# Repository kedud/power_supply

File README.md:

# Power Supply

Symetrical +15/-15V power supply intented to power RM4 mixer.

Some of the part are not present on the schematic:
 - Fuse
 - IEC panel mount adapter
 - DIN panel mount output connector
 - Power switch
 - Case

| Parts 			| 	 Part ref		|
| ----------------- | ----------------- |
| Fuse 				|               	|
| IEC connector 	|               	|
| DIN connector 	|               	|
| Power switch		|					|

The BoM for this schematics can be found [here](https://octopart.com/bom-tool/Scw2LM2J)

A Mouser cart is also available [here](https://www.mouser.com/ProjectManager/ProjectDetail.aspx?AccessID=ff7172ce4d)

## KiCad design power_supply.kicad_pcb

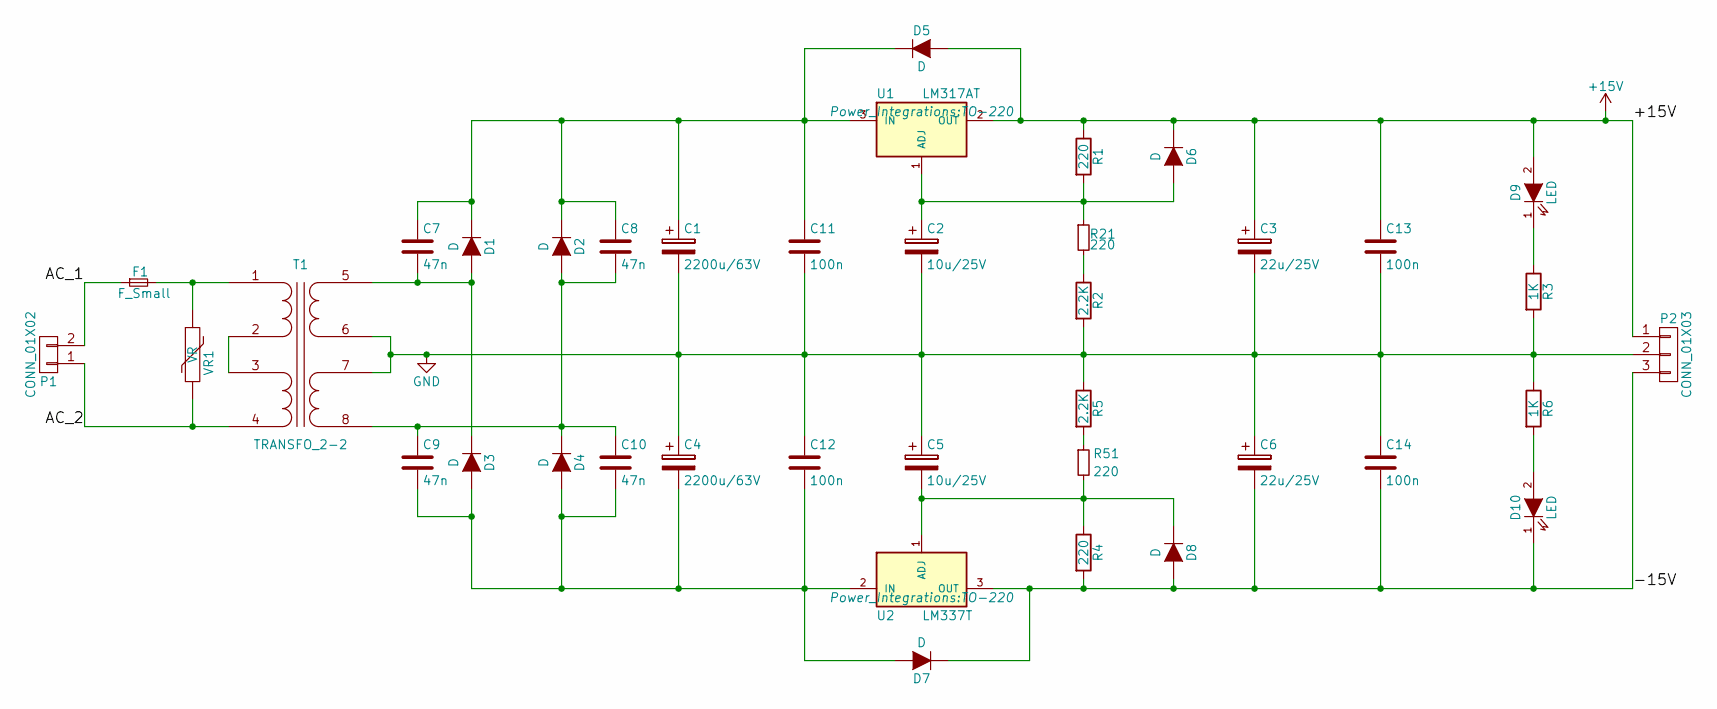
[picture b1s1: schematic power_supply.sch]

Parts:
C1, C4: 2200u/63V; C_Radial_D18_L36_P7.5; Mfg_Part_No UVR1J222MHD
C2, C5: 10u/25V; C_Radial_D5_L11_P2; Mfg_Part_No TVX1E101MAD
C3, C6: 22u/25V; C_Radial_D5_L11_P2; Mfg_Part_No UVR1E220MDD
C7, C8, C9, C10: 47n; C_Rect_L7_W4.5_P5; Mfg_Part_No QYX2A473KTP
C11, C12, C13, C14: 100n; C_Rect_L7_W4.5_P5; Mfg_Part_No QYX2A104KTP
D1, D2, D3, D4: D; Diode_DO-35_SOD27_Horizontal_RM10; Mfg_Part_No BY255P-E3/54 BY255P-E3/54
D5, D6, D7, D8: D; Diode_DO-35_SOD27_Horizontal_RM10; Mfg_Part_No 1N4007
D9, D10: LED; LED-3MM
F1: F_Small; CP4; Mfg_Part_No 0031.1666
P1: CONN_01X02; CONN_2; Mfg_Part_No PX0580/28
P2: CONN_01X03; CONN_3
R1, R4: 220; Resistor_Horizontal_RM7mm; Mfg_Part_No 0
R2, R5: 2.2K; Resistor_Horizontal_RM7mm; Mfg_Part_No CCF072K20JKE36
R3: 1K; Resistor_Horizontal_RM7mm
R6: 1K; Resistor_Horizontal_RM7mm; Mfg_Part_No 0
R21, R51: 220; Resistor_Horizontal_RM7mm
T1: TRANSFO_2-2; TRANSF-4x4; Mfg_Part_No FS36-550-C2 FS36-550-C2 FS36-550-C2
U1: LM317AT; TO-220; Mfg_Part_No LM317KCSE3 LM317KCSE3
U2: LM337T; TO-220; Mfg_Part_No LM337T/NOPB
VR1: VR; Resistor_Horizontal_RM7mm; Mfg_Part_No V250LA40AP

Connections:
+15V: C3.1, C13.1, D5.2 (A), D6.1 (K), D9.2 (A), P2.1, R1.1, U1.2 (OUT)
/-15V: C6.2, C14.2, D7.1 (K), D8.2 (A), D10.1 (K), P2.3, R4.2, U2.3 (OUT)
/AC_1: F1.1, P1.2
/AC_2: P1.1, T1.4 (PD), VR1.2
GND: C1.2, C2.2, C3.2, C4.1, C5.1, C6.1, C11.2, C12.1, C13.2, C14.1, P2.2, R2.2, R3.2, R5.1, R6.1, T1.6 (SB), T1.7 (SC)
unnamed: C1.1, C7.1, C8.1, C11.1, D1.1 (K), D2.1 (K), D5.1 (K), U1.3 (IN)
unnamed: C2.1, D6.2 (A), R1.2, R21.1, U1.1 (ADJ)
unnamed: C5.2, D8.1 (K), R4.1, R51.2, U2.1 (ADJ)
unnamed: C7.2, D1.2 (A), D3.1 (K), T1.5 (SA)
unnamed: C8.2, C9.1, C10.1, D2.2 (A), D4.1 (K), T1.8 (SD)
unnamed: C4.2, C9.2, C10.2, C12.2, D3.2 (A), D4.2 (A), D7.2 (A), U2.2 (IN)
unnamed: D9.1 (K), R3.1
unnamed: D10.2 (A), R6.2
unnamed: F1.2, T1.1 (PA), VR1.1
unnamed: R2.1, R21.2
unnamed: R5.2, R51.1
unnamed: T1.2 (PB), T1.3 (PC)

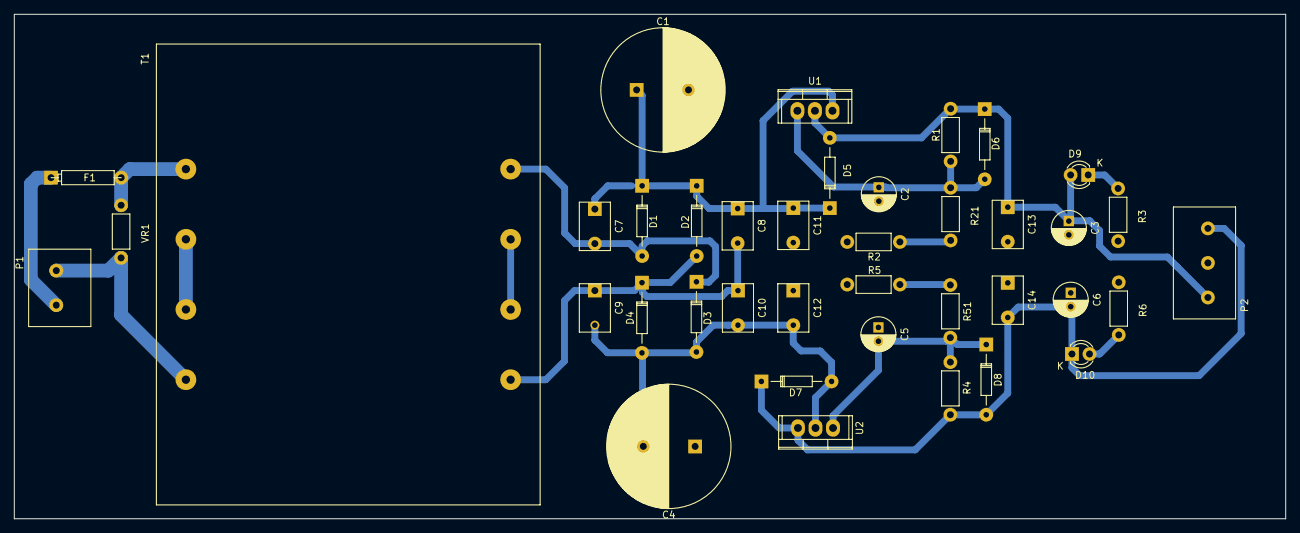
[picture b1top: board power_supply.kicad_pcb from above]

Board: 2 copper layers, 184.0 x 73.0 mm, 39 parts (0 on the bottom side), 17 nets.

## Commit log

2017-11-17 Updated components ref
2017-11-17 Add README.md
